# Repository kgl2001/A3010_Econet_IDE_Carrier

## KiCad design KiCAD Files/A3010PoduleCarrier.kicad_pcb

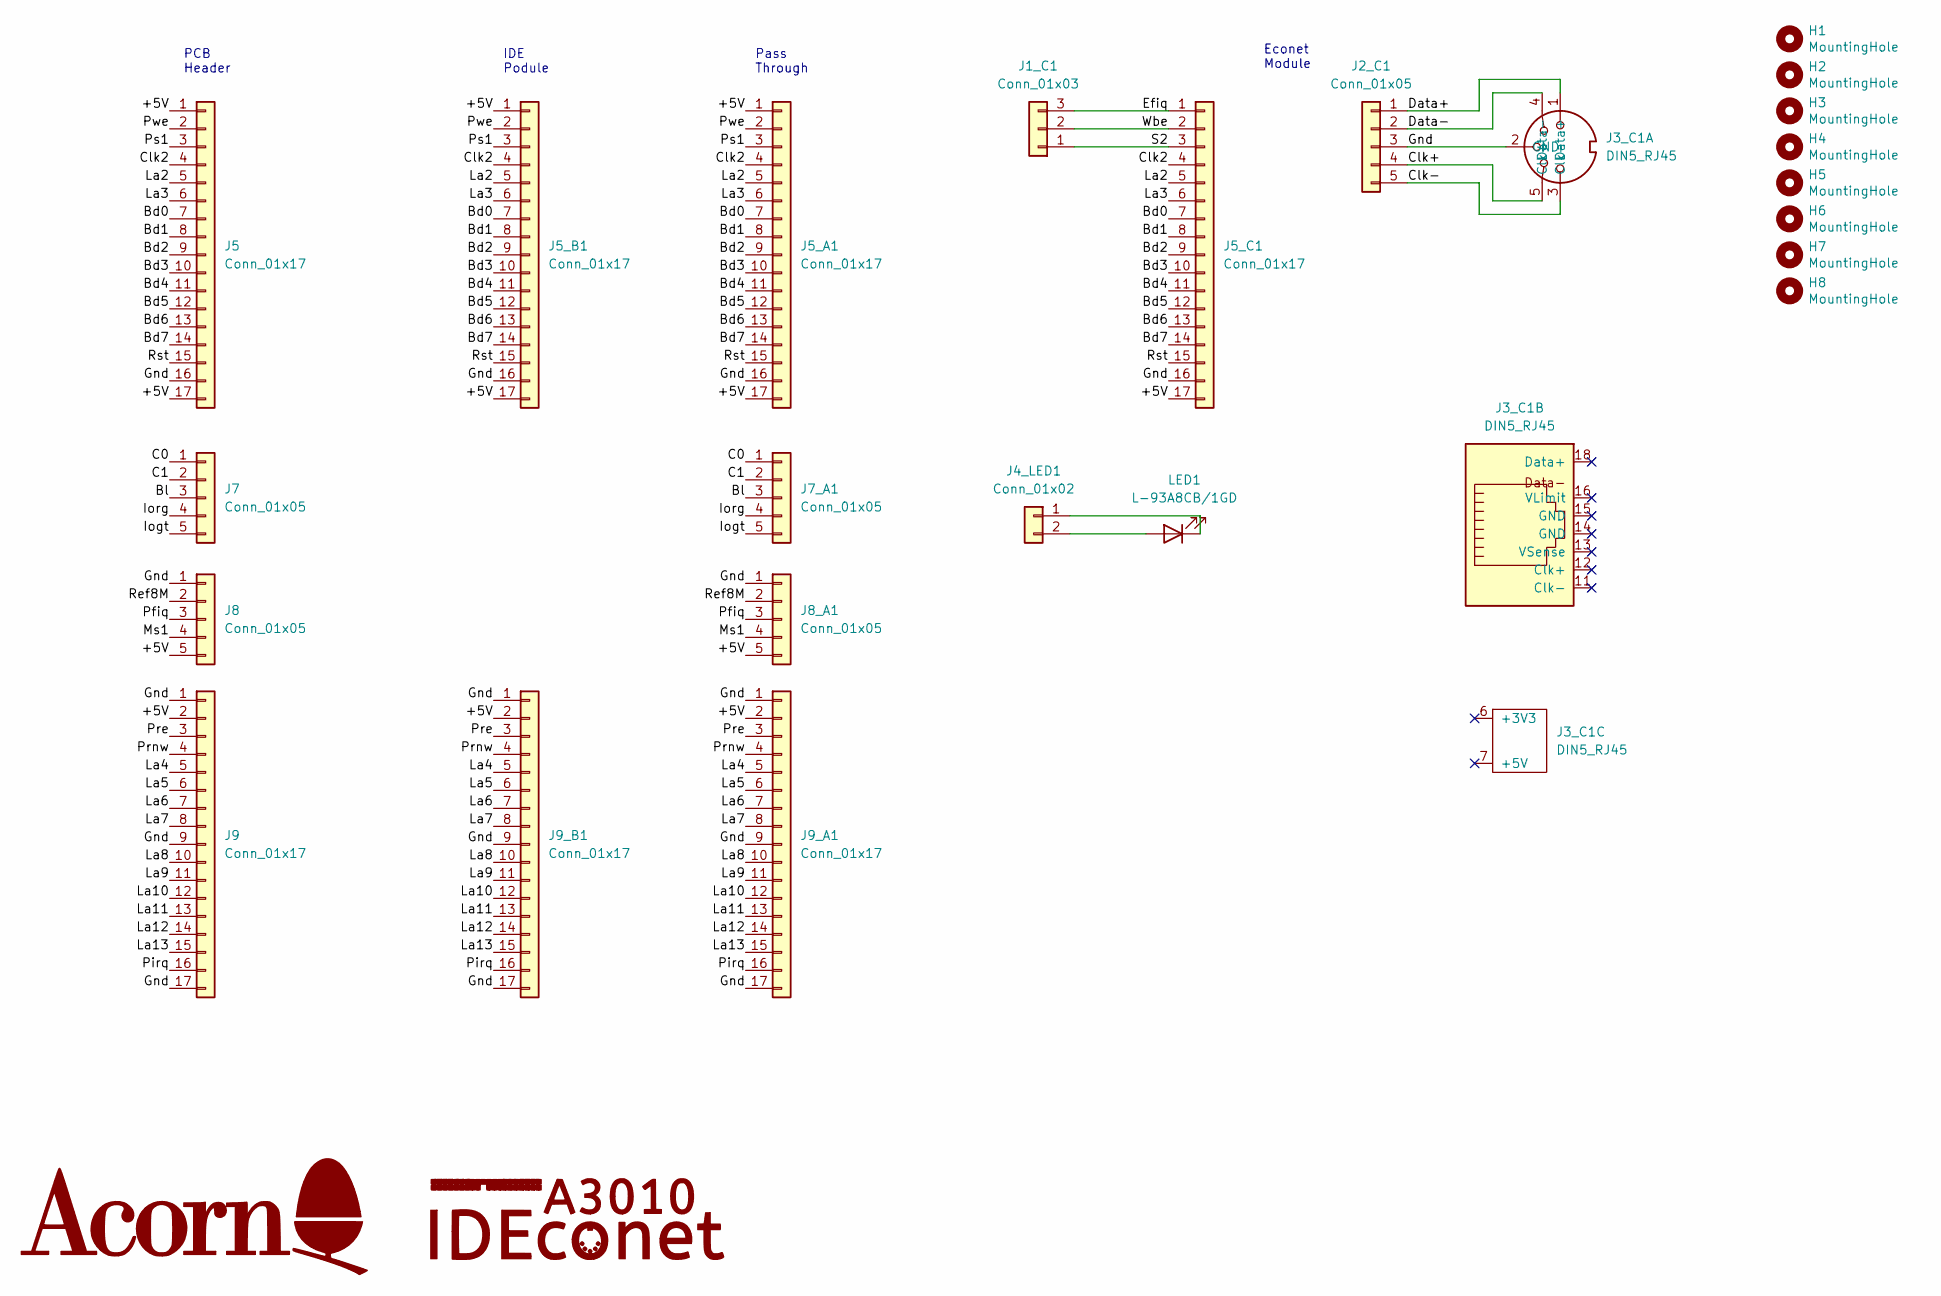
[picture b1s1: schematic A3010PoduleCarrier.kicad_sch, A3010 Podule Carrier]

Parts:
G1: Acorn_LOGO; Acorn Logo
G2: IDEconet_LOGO; IDEconet
H1, H2, H3, H4, H7, H8: MountingHole; MountingHole_2.7mm
H5, H6: MountingHole; MountingHole_4mm
J1_C1: Conn_01x03; PinHeader_1x03_P2.54mm_Horizontal
J2_C1, J7_A1, J8_A1: Conn_01x05; PinSocket_1x05_P2.54mm_Vertical
J3_C1: DIN5_RJ45; CombinedDIN5RJ45PinHeader90Deg
J4_LED1: Conn_01x02; PinSocket_1x02_P2.54mm_Vertical
J5, J9: Conn_01x17; PinHeader_1x17_P2.54mm_Vertical
J5_A1, J5_B1, J5_C1, J9_A1, J9_B1: Conn_01x17; PinSocket_1x17_P2.54mm_Vertical
J7, J8: Conn_01x05; PinHeader_1x05_P2.54mm_Vertical
LED1: L-93A8CB/1GD; LED_D3.0mm_Horizontal_O1.27mm_Z6.0mm

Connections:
/+5V: J5.1, J5.17, J5_A1.1, J5_A1.17, J5_B1.1, J5_B1.17, J5_C1.17, J8.5, J8_A1.5, J9.2, J9_A1.2, J9_B1.2
/Bd0: J5.7, J5_A1.7, J5_B1.7, J5_C1.7
/Bd1: J5.8, J5_A1.8, J5_B1.8, J5_C1.8
/Bd2: J5.9, J5_A1.9, J5_B1.9, J5_C1.9
/Bd3: J5.10, J5_A1.10, J5_B1.10, J5_C1.10
/Bd4: J5.11, J5_A1.11, J5_B1.11, J5_C1.11
/Bd5: J5.12, J5_A1.12, J5_B1.12, J5_C1.12
/Bd6: J5.13, J5_A1.13, J5_B1.13, J5_C1.13
/Bd7: J5.14, J5_A1.14, J5_B1.14, J5_C1.14
/Bl: J7.3, J7_A1.3
/C0: J7.1, J7_A1.1
/C1: J7.2, J7_A1.2
/Clk2: J5.4, J5_A1.4, J5_B1.4, J5_C1.4
/Clk+: J2_C1.4, J3_C1.5 (Clk+)
/Clk-: J2_C1.5, J3_C1.3 (Clk-)
/Data+: J2_C1.1, J3_C1.1 (Data+)
/Data-: J2_C1.2, J3_C1.4 (Data-)
/Efiq: J1_C1.3, J5_C1.1
/Gnd: J2_C1.3, J3_C1.2 (GND), J5.16, J5_A1.16, J5_B1.16, J5_C1.16, J8.1, J8_A1.1, J9.1, J9.9, J9.17, J9_A1.1, J9_A1.9, J9_A1.17, J9_B1.1, J9_B1.9, J9_B1.17
/Iogt: J7.5, J7_A1.5
/Iorg: J7.4, J7_A1.4
/La2: J5.5, J5_A1.5, J5_B1.5, J5_C1.5
/La3: J5.6, J5_A1.6, J5_B1.6, J5_C1.6
/La4: J9.5, J9_A1.5, J9_B1.5
/La5: J9.6, J9_A1.6, J9_B1.6
/La6: J9.7, J9_A1.7, J9_B1.7
/La7: J9.8, J9_A1.8, J9_B1.8
/La8: J9.10, J9_A1.10, J9_B1.10
/La9: J9.11, J9_A1.11, J9_B1.11
/La10: J9.12, J9_A1.12, J9_B1.12
/La11: J9.13, J9_A1.13, J9_B1.13
/La12: J9.14, J9_A1.14, J9_B1.14
/La13: J9.15, J9_A1.15, J9_B1.15
/Ms1: J8.4, J8_A1.4
/Pfiq: J8.3, J8_A1.3
/Pirq: J9.16, J9_A1.16, J9_B1.16
/Pre: J9.3, J9_A1.3, J9_B1.3
/Prnw: J9.4, J9_A1.4, J9_B1.4
/Ps1: J5.3, J5_A1.3, J5_B1.3
/Pwe: J5.2, J5_A1.2, J5_B1.2
/Ref8M: J8.2, J8_A1.2
/Rst: J5.15, J5_A1.15, J5_B1.15, J5_C1.15
/S2: J1_C1.1, J5_C1.3
/Wbe: J1_C1.2, J5_C1.2
unnamed: J4_LED1.1, LED1.1 (K)
unnamed: J4_LED1.2, LED1.2 (A)

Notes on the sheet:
Econet Module
IDE Podule
PCB Header
Pass Through

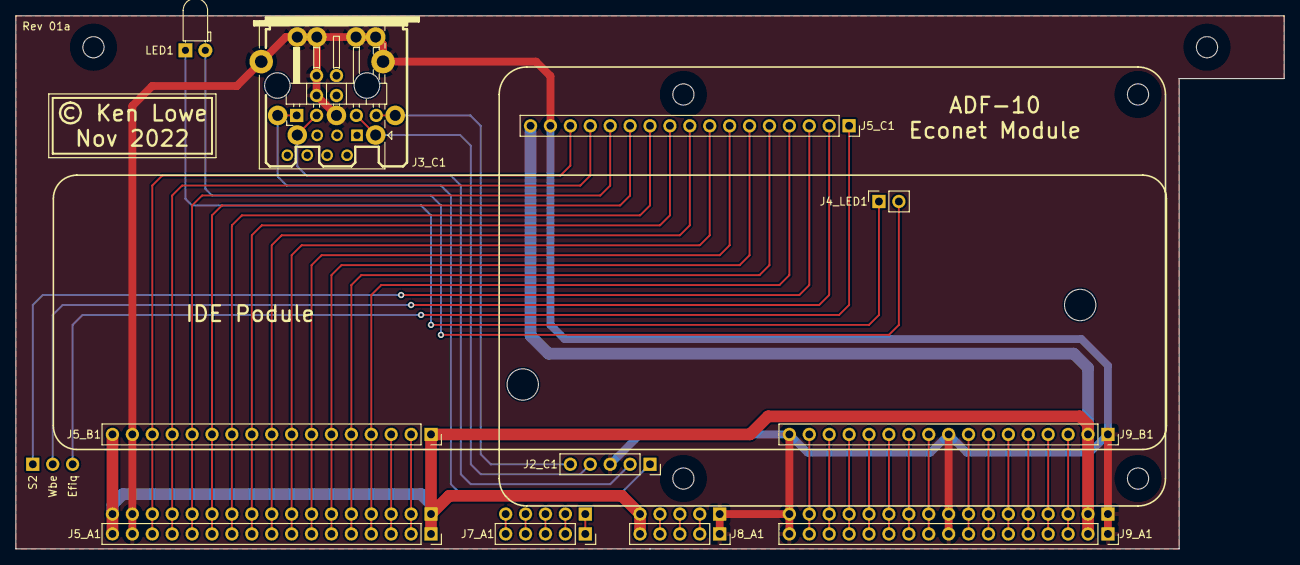
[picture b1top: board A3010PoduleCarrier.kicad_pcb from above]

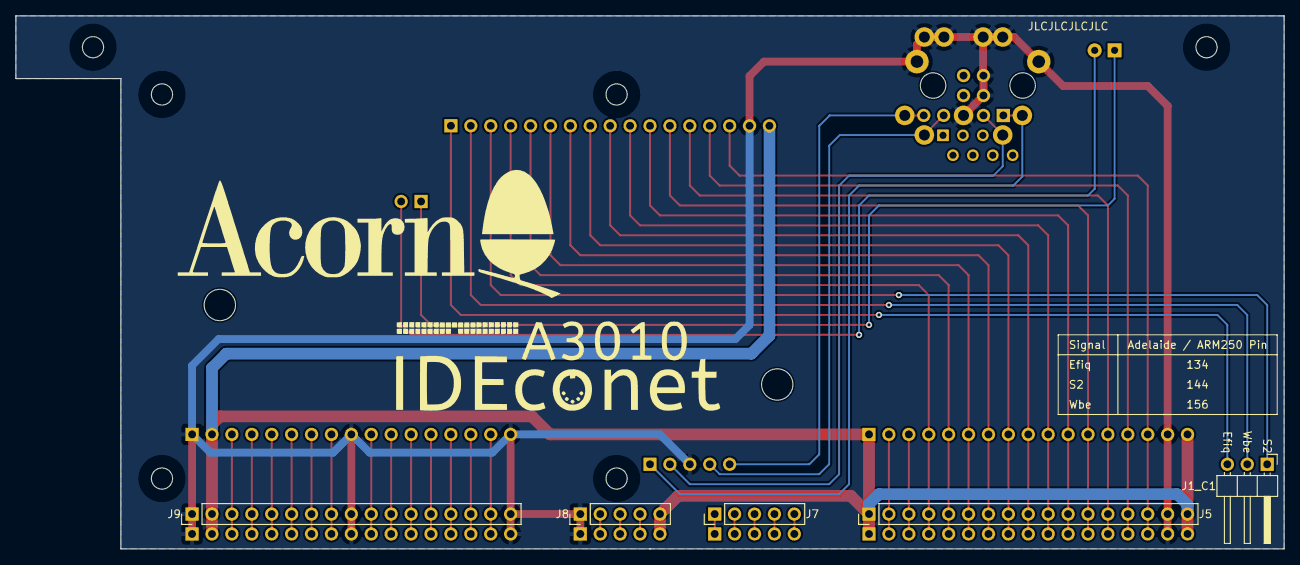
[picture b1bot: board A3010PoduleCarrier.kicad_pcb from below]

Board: 2 copper layers, 161.8 x 68.0 mm, 26 parts (7 on the bottom side), 46 nets.

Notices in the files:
KiCAD Files/A3010PoduleCarrier.kicad_pcb:
© Ken Lowe
